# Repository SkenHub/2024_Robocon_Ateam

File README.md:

# 2024_Robocon_Ateam
2024年高専ロボコン  Aチーム

* 野口 史遠
* 三村 柚葉
* 堀 洸志朗
* 黒住 太一
* 川口 知恩
* 真志取 朔
* 入谷 美志成
* 斉藤 実桜
* 岩本 千尋
* 山城 喬楽
* 北条 博輝
* 内海翔太郎

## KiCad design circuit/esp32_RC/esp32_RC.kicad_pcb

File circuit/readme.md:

これは2024の回路のreadmeです

基本的にはモジュールを使用しているため詳細は省きます
https://github.com/SkenHub/Circuit-Module-Readme

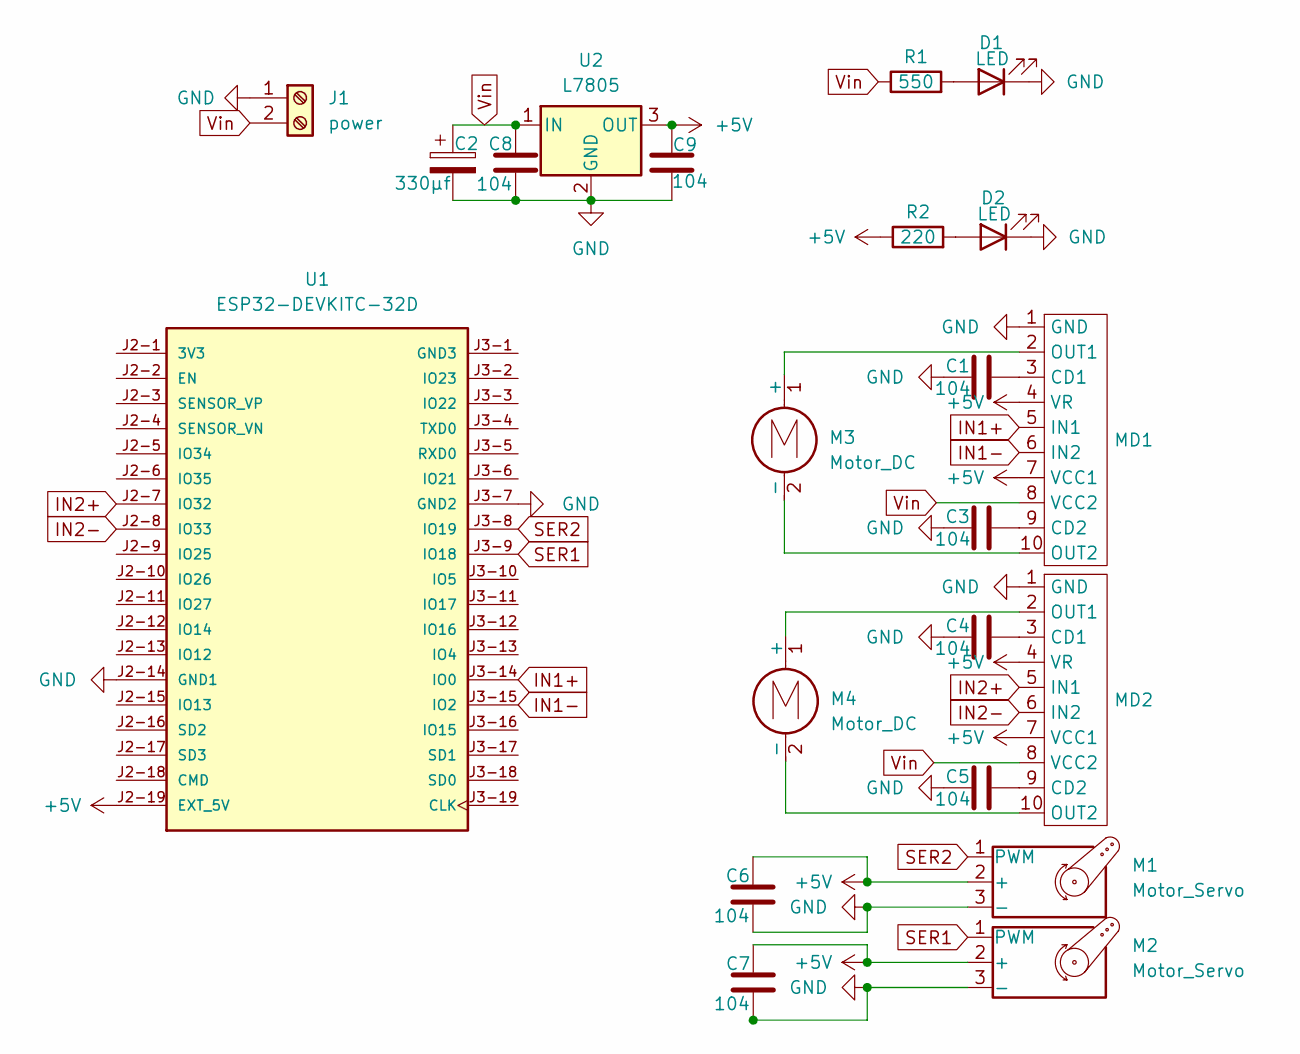
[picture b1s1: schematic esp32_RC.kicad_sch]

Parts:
C1, C3, C4, C5, C6, C7, C8, C9: 104; C_0603_1608Metric
C2: 330μf; CP_Elec_10x10
D1, D2: LED; LED_0603_1608Metric
J1: power; AMASS_XT30PW-M_1x02_P2.50mm_Horizontal
M1, M2: Motor_Servo; JST_XA_S03B-XASK-1_1x03_P2.50mm_Horizontal
M3, M4: Motor_DC; AMASS_XT30PW-F_1x02_P2.50mm_Horizontal
MD1, MD2: BA6222
R1: 550; R_0603_1608Metric
R2: 220; R_0603_1608Metric
U1: ESP32-DEVKITC-32D; MODULE_ESP32-DEVKITC-32D; PARTREV V4
U2: L7805; TO-252-2

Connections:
+5V: C6.2, C7.2, C9.2, M1.2 (+), M2.2 (+), MD1.4 (VR), MD1.7 (VCC1), MD2.4 (VR), MD2.7 (VCC1), R2.1, U1.J2-19 (EXT_5V), U2.3 (OUT)
GND: C1.1, C2.2, C3.1, C4.1, C5.1, C6.1, C7.1, C8.1, C9.1, D1.1 (K), D2.1 (K), J1.1, M1.3 (-), M2.3 (-), MD1.1 (GND), MD2.1 (GND), U1.J2-14 (GND1), U1.J3-7 (GND2), U2.2 (GND)
IN1+: MD1.5 (IN1), U1.J3-14 (IO0)
IN1-: MD1.6 (IN2), U1.J3-15 (IO2)
IN2+: MD2.5 (IN1), U1.J2-7 (IO32)
IN2-: MD2.6 (IN2), U1.J2-8 (IO33)
unnamed: D1.2 (A), R1.2
unnamed: D2.2 (A), R2.2
unnamed: M3.1 (+), MD1.2 (OUT1)
unnamed: M3.2 (-), MD1.10 (OUT2)
unnamed: M4.1 (+), MD2.2 (OUT1)
unnamed: M4.2 (-), MD2.10 (OUT2)
unnamed: C1.2, MD1.3 (CD1)
unnamed: C3.2, MD1.9 (CD2)
unnamed: C4.2, MD2.3 (CD1)
unnamed: C5.2, MD2.9 (CD2)
SER1: M2.1 (PWM), U1.J3-9 (IO18)
SER2: M1.1 (PWM), U1.J3-8 (IO19)
Vin: C2.1, C8.2, J1.2, MD1.8 (VCC2), MD2.8 (VCC2), R1.1, U2.1 (IN)

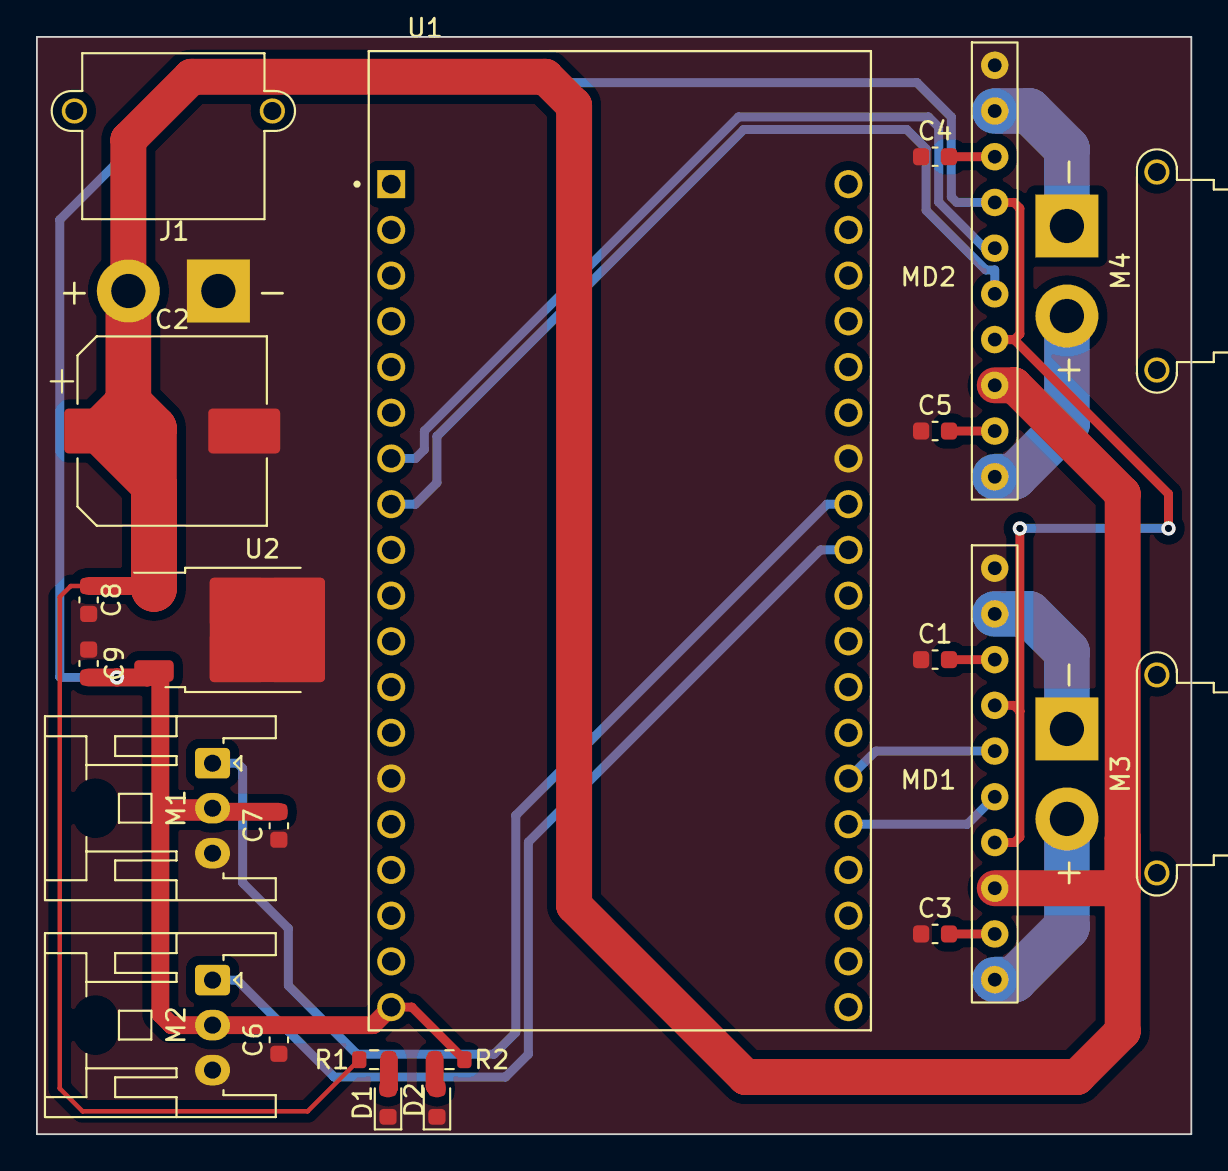
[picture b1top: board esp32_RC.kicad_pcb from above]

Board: 2 copper layers, 64.1 x 61.0 mm, 22 parts (0 on the bottom side), 19 nets.

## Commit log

2024-05-06 スポンジパンジャン
2024-05-10 3輪オムニ（足回りのみ）
    回路と通信のことは考えていない
2024-05-10 Revert "3輪オムニ（足回りのみ）"
    This reverts commit c5e0bb8eb583d2d6678bcb4fac473374bd8d9508.
2024-05-10 3輪オムニ（足回りのみ）
    通信と回路のことは考えていない
2024-05-10 改造したCAN通信関係を追加
2024-05-11 can受信の修正
2024-05-11 テスト用にSBDBTに対応
2024-05-12 足回り動作確認版
2024-05-15 タイヤの進んだ距離・速度を取得
    SBDBT関連はコメントアウトしました
2024-05-15 向いている角度の推定
    SBDBTの切り替えをマクロに変更
2024-05-21 作業環境のリフレッシュ
2024-05-23 R1プログラム作成
    4WD omni-wheels
2024-05-27 Add files via upload
    卒研用に作ってたやつを改良してR1ように変換。リアルセンスは未実装
    詳しくはreadme
2024-05-31 Update cmd_vel_to_serial_node.py
    角度を度数法に
2024-05-31 Update controller_node.py
    速度最大値１００
    方向と角度を360度
2024-05-31 Update readme.md
    角度変更
2024-05-31 Update controller_node.py
    台形制御
2024-06-20 ロボットごとにフォルダ分け
2024-06-22 R1マイコン間通信の規格設定
2024-06-22 配線順の変更
2024-06-22 R1マイコン間通信規格更新
2024-06-22 myuart.hpp追加
2024-06-22 myuart.hppに対応
2024-06-23 SW4 <-> PlatformIO間の通信成功
2024-06-23 miniB対応（PC向け）
2024-06-23 R1_DDのSW4移行前最終版
2024-06-24 R1_DD main.cppをSW4へ移行
2024-06-24 SW4へのリファクタリング完了
2024-06-25 floatの受信方法の修正
2024-06-25 モーターをPD制御に変更
2024-06-27 PC通信マイコンをMDD1に変更
2024-06-30 回転の制御を角速度[deg/s]に変更
2024-07-02 更新: MDD1 & sensor
2024-07-02 R1_MDD1/RB_MDDをPID制御に修正
2024-07-06 R1_DD/MDD1:細々とした修正
2024-07-06 動作確認版up
    エンコーダ分解能8192->2048
    ゲイン設定（変更予定）
    エンコーダデータを0.1秒間の平均に変更
2024-09-04 Create R1_MDD1_main.cpp
    V,Θ，ωからVy,Vx,ωを導出する部分がおかしいです
2024-09-11 CAN通信に変更
2024-09-12 Update R1_UI.html
    コントローラーによる動作モードの切り替えを追加
2024-09-13 Update R1_UI.html
    デバック表示の追加
2024-09-14 リミット追加
2024-09-21 Add files via upload
    ロボマス足回り追加
2024-12-13 アースポート追加
    2024アースポート
